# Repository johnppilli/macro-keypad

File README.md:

# Macro Keypad — Custom USB Mechanical Keypad (KiCad)

A custom 9-key (3×3) USB-C mechanical macro keypad, designed from schematic to
fabrication in KiCad around an **RP2040** microcontroller. This is my own design —
schematic capture, component selection, PCB layout, and fabrication.

## The fabricated board

| Top | Bottom |
| --- | --- |
|  |  |

*Bare 2-layer board from JLCPCB, prior to switch/component assembly.*

## Design highlights

- **RP2040** microcontroller with USB-C for both power and data
- **USBLC6** ESD protection on the USB data lines
- **3×3 matrix of 9 mechanical key switches**, each with a per-key diode for N-key
  rollover / anti-ghosting during matrix scanning
- Decoupling on each supply pin; crystal and supporting passives per the RP2040
  reference design
- **2-layer PCB**, board outline defined in Edge.Cuts, ERC/DRC clean
- Gerbers + drill files generated and **fabricated through JLCPCB**

## What's in this repo

- `macro-keypad.kicad_sch` / `.kicad_pcb` / `.kicad_pro` — the KiCad project
- `macro-keypad.pdf` — schematic PDF
- `gerbers/` — fabrication outputs
- `board-front.jpg` / `board-back.jpg` — photos of the fabricated board

## Status — in progress

Bare fabricated board is in hand. Currently:

- **Hand-soldering** the switches, per-key diodes, and supporting components onto the board
- **Writing the RP2040 firmware** — USB-HID keyboard with matrix scanning and debounce

Next up: bring-up and testing once assembly is complete.

## Tools

KiCad · JLCPCB

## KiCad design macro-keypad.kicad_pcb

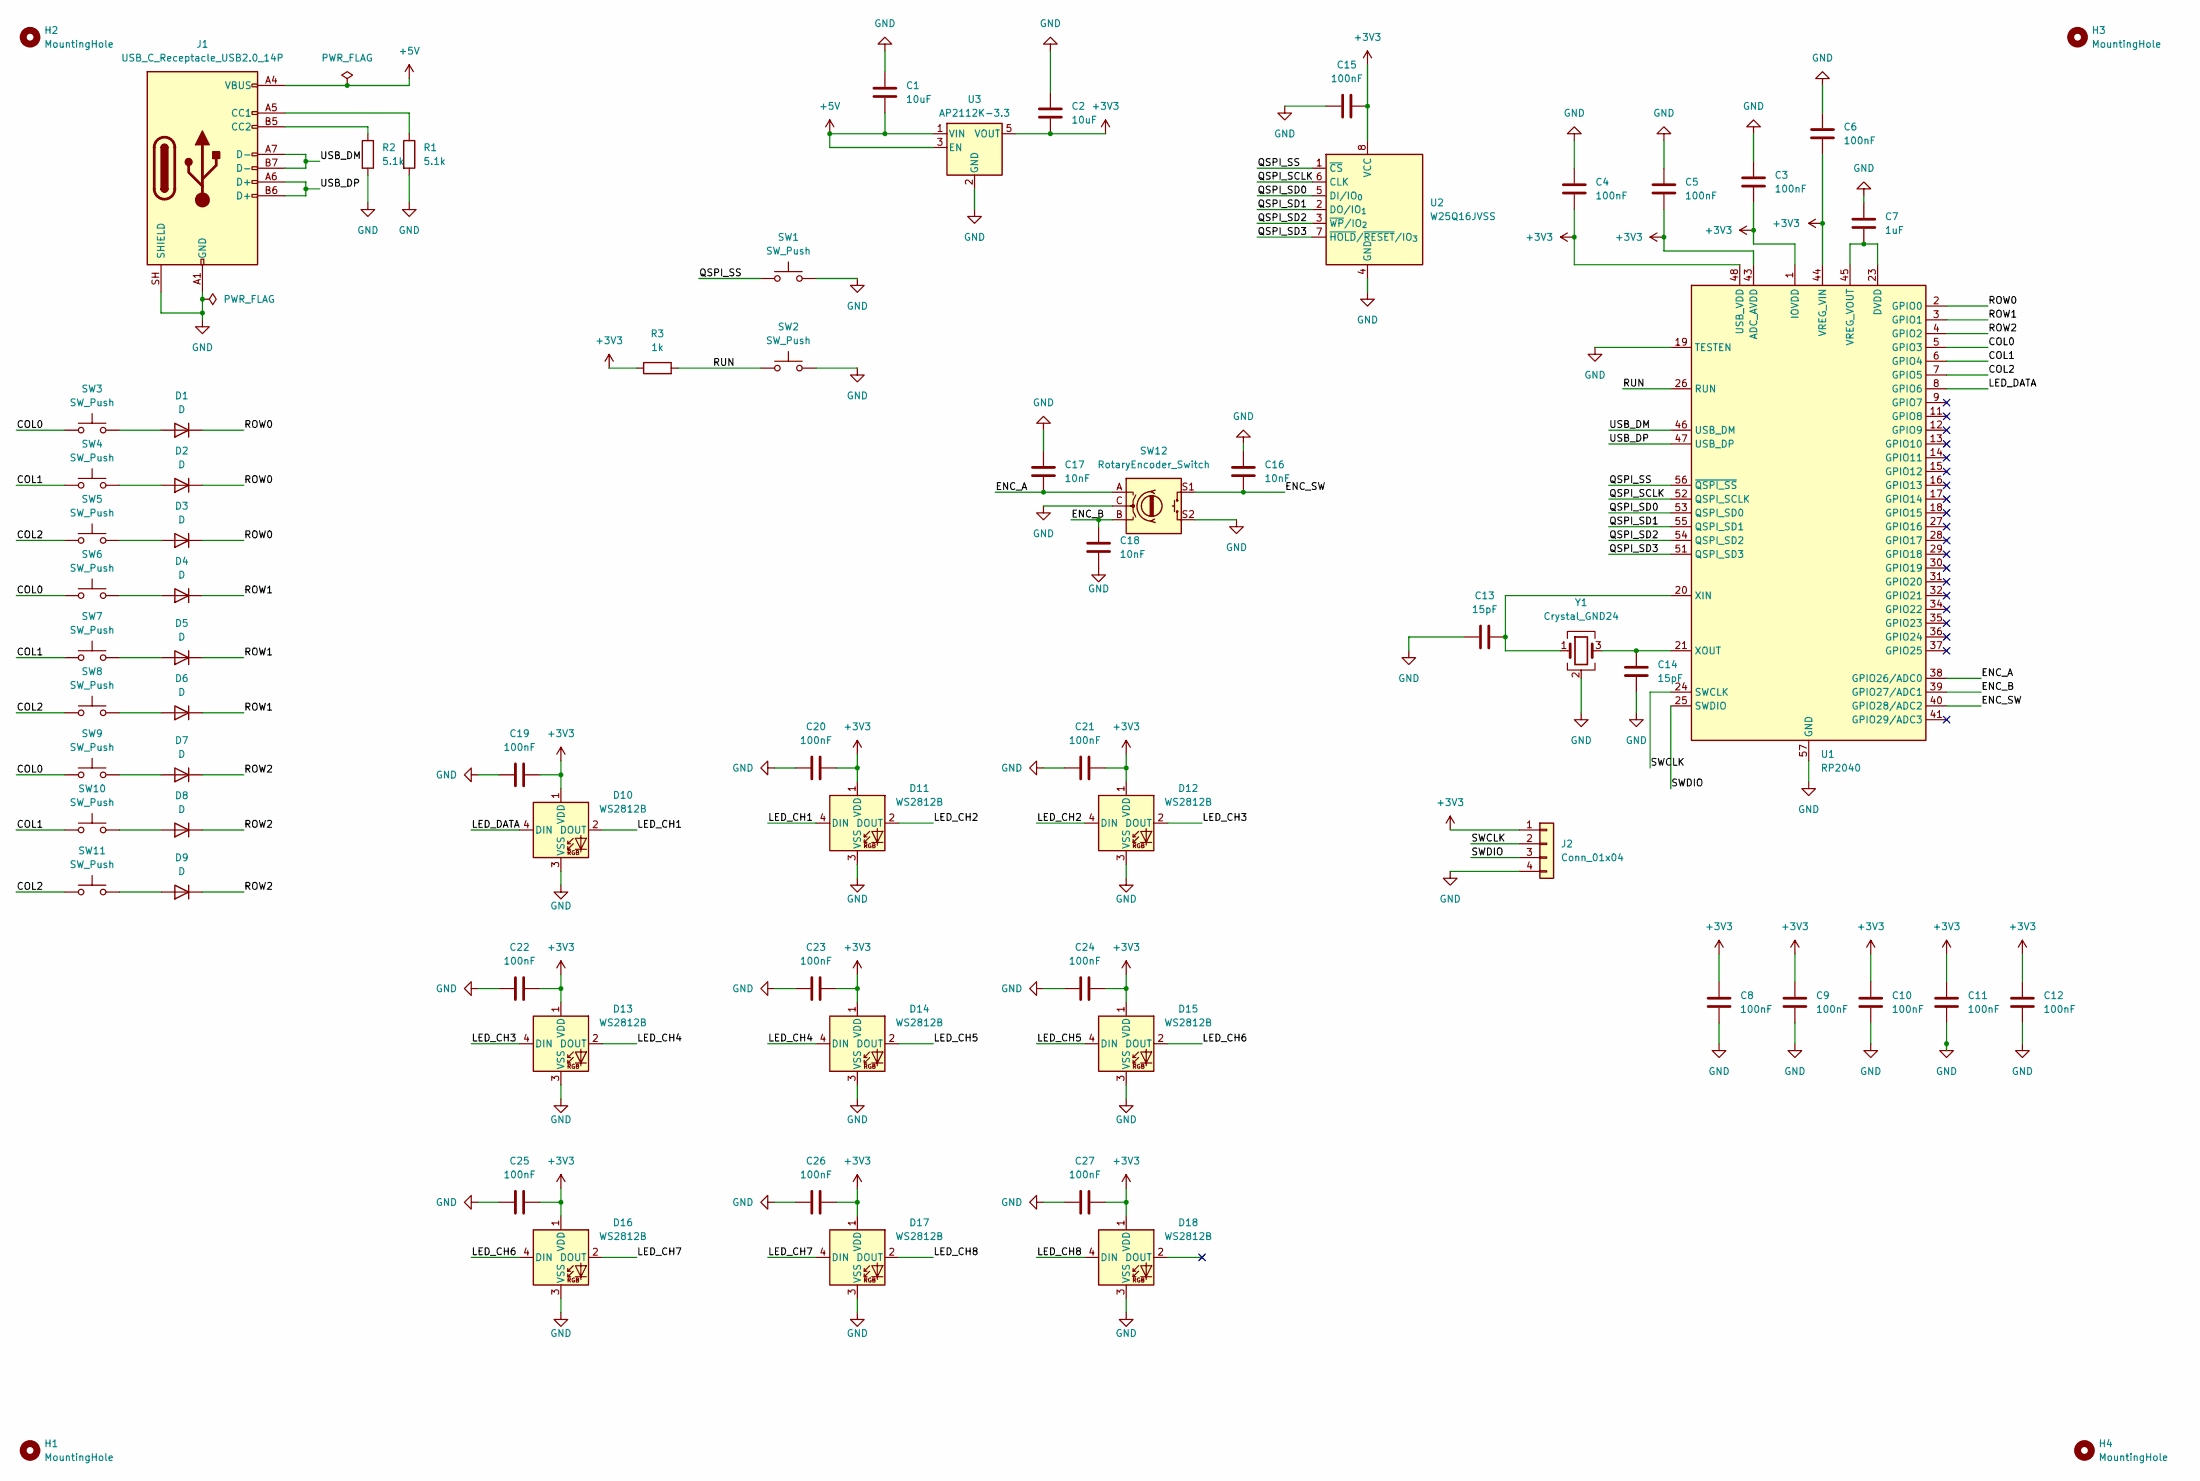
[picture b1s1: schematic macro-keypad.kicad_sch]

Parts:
C1, C2: 10uF; C_0603_1608Metric
C3, C4, C5, C6, C8, C9, C10, C11, C12, C15, C19, C20, C21, C22, C23, C24, C25, C26, C27: 100nF; C_0603_1608Metric
C7: 1uF; C_0603_1608Metric
C13, C14: 15pF; C_0603_1608Metric
C16, C17, C18: 10nF; C_0603_1608Metric
D1, D2, D3, D4, D5, D6, D7, D8, D9: D; D_SOD-123
D10, D11, D12, D13, D14, D15, D16, D17, D18: WS2812B; LED_WS2812B_PLCC4_5.0x5.0mm_P3.2mm
H1, H2, H3, H4: MountingHole; MountingHole_2.2mm_M2
J1: USB_C_Receptacle_USB2.0_14P; USB_C_Receptacle_GCT_USB4085
J2: Conn_01x04; PinHeader_1x04_P2.54mm_Vertical
R1, R2: 5.1k; R_0603_1608Metric
R3: 1k; R_0603_1608Metric
SW1, SW2: SW_Push; SW_PUSH_6mm
SW3, SW4, SW5, SW6, SW7, SW8, SW9, SW10, SW11: SW_Push; Kailh_socket_MX_optional
SW12: RotaryEncoder_Switch; RotaryEncoder_Alps_EC11E-Switch_Vertical_H20mm
U1: RP2040; QFN-56-1EP_7x7mm_P0.4mm_EP3.2x3.2mm
U2: W25Q16JVSS; SOIC-8_5.3x5.3mm_P1.27mm
U3: AP2112K-3.3; SOT-23-5
Y1: Crystal_GND24; Crystal_SMD_3225-4Pin_3.2x2.5mm

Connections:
+3V3: C2.1, C3.2, C4.2, C5.2, C6.2, C8.1, C9.1, C10.1, C11.1, C12.1, C15.2, C19.2, C20.2, C21.2, C22.2, C23.2, C24.2, C25.2, C26.2, C27.2, D10.1 (VDD), D11.1 (VDD), D12.1 (VDD), D13.1 (VDD), D14.1 (VDD), D15.1 (VDD), D16.1 (VDD), D17.1 (VDD), D18.1 (VDD), J2.1, R3.1, U1.1 (IOVDD), U1.10 (IOVDD), U1.22 (IOVDD), U1.33 (IOVDD), U1.42 (IOVDD), U1.43 (ADC_AVDD), U1.44 (VREG_VIN), U1.48 (USB_VDD), U1.49 (IOVDD), U2.8 (VCC), U3.5 (VOUT)
+5V: C1.2, J1.A4 (VBUS), J1.A9 (VBUS), J1.B4 (VBUS), J1.B9 (VBUS), U3.1 (VIN), U3.3 (EN)
/COL0: SW3.1, SW6.1, SW9.1, U1.5 (GPIO3)
/COL1: SW4.1, SW7.1, SW10.1, U1.6 (GPIO4)
/COL2: SW5.1, SW8.1, SW11.1, U1.7 (GPIO5)
/ENC_A: C17.2, SW12.A, U1.38 (GPIO26/ADC0)
/ENC_B: C18.1, SW12.B, U1.39 (GPIO27/ADC1)
/ENC_SW: C16.2, SW12.S1, U1.40 (GPIO28/ADC2)
/LED_CH1: D10.2 (DOUT), D11.4 (DIN)
/LED_CH2: D11.2 (DOUT), D12.4 (DIN)
/LED_CH3: D12.2 (DOUT), D13.4 (DIN)
/LED_CH4: D13.2 (DOUT), D14.4 (DIN)
/LED_CH5: D14.2 (DOUT), D15.4 (DIN)
/LED_CH6: D15.2 (DOUT), D16.4 (DIN)
/LED_CH7: D16.2 (DOUT), D17.4 (DIN)
/LED_CH8: D17.2 (DOUT), D18.4 (DIN)
/LED_DATA: D10.4 (DIN), U1.8 (GPIO6)
/QSPI_SCLK: U1.52 (QSPI_SCLK), U2.6 (CLK)
/QSPI_SD0: U1.53 (QSPI_SD0), U2.5 (DI/IO_{0})
/QSPI_SD1: U1.55 (QSPI_SD1), U2.2 (DO/IO_{1})
/QSPI_SD2: U1.54 (QSPI_SD2), U2.3 (~WP/IO_{2})
/QSPI_SD3: U1.51 (QSPI_SD3), U2.7 (~HOLD/~RESET/IO_{3})
/QSPI_SS: SW1.1, U1.56 (~QSPI_SS), U2.1 (~CS)
/ROW0: D1.1 (K), D2.1 (K), D3.1 (K), U1.2 (GPIO0)
/ROW1: D4.1 (K), D5.1 (K), D6.1 (K), U1.3 (GPIO1)
/ROW2: D7.1 (K), D8.1 (K), D9.1 (K), U1.4 (GPIO2)
/RUN: R3.2, SW2.1, U1.26 (RUN)
/SWCLK: J2.2, U1.24 (SWCLK)
/SWDIO: J2.3, U1.25 (SWDIO)
/USB_DM: J1.A7 (D-), J1.B7 (D-), U1.46 (USB_DM)
/USB_DP: J1.A6 (D+), J1.B6 (D+), U1.47 (USB_DP)
GND: C1.1, C2.2, C3.1, C4.1, C5.1, C6.1, C7.1, C8.2, C9.2, C10.2, C11.2, C12.2, C13.2, C14.2, C15.1, C16.1, C17.1, C18.2, C19.1, C20.1, C21.1, C22.1, C23.1, C24.1, C25.1, C26.1, C27.1, D10.3 (VSS), D11.3 (VSS), D12.3 (VSS), D13.3 (VSS), D14.3 (VSS), D15.3 (VSS), D16.3 (VSS), D17.3 (VSS), D18.3 (VSS), J1.A1 (GND), J1.A12 (GND), J1.B1 (GND), J1.B12 (GND), J1.SH (SHIELD), J2.4, R1.2, R2.2, SW1.2, SW2.2, SW12.C, SW12.S2, U1.19 (TESTEN), U1.57 (GND), U2.4 (GND), U3.2 (GND), Y1.2 (G), Y1.4 (G)
unnamed: D1.2 (A), SW3.2
unnamed: D2.2 (A), SW4.2
unnamed: D3.2 (A), SW5.2
unnamed: D4.2 (A), SW6.2
unnamed: D5.2 (A), SW7.2
unnamed: D6.2 (A), SW8.2
unnamed: D7.2 (A), SW9.2
unnamed: D8.2 (A), SW10.2
unnamed: D9.2 (A), SW11.2
unnamed: J1.A5 (CC1), R1.1
unnamed: J1.B5 (CC2), R2.1
unnamed: C7.2, U1.23 (DVDD), U1.45 (VREG_VOUT), U1.50 (DVDD)
unnamed: C13.1, U1.20 (XIN), Y1.1
unnamed: C14.1, U1.21 (XOUT), Y1.3

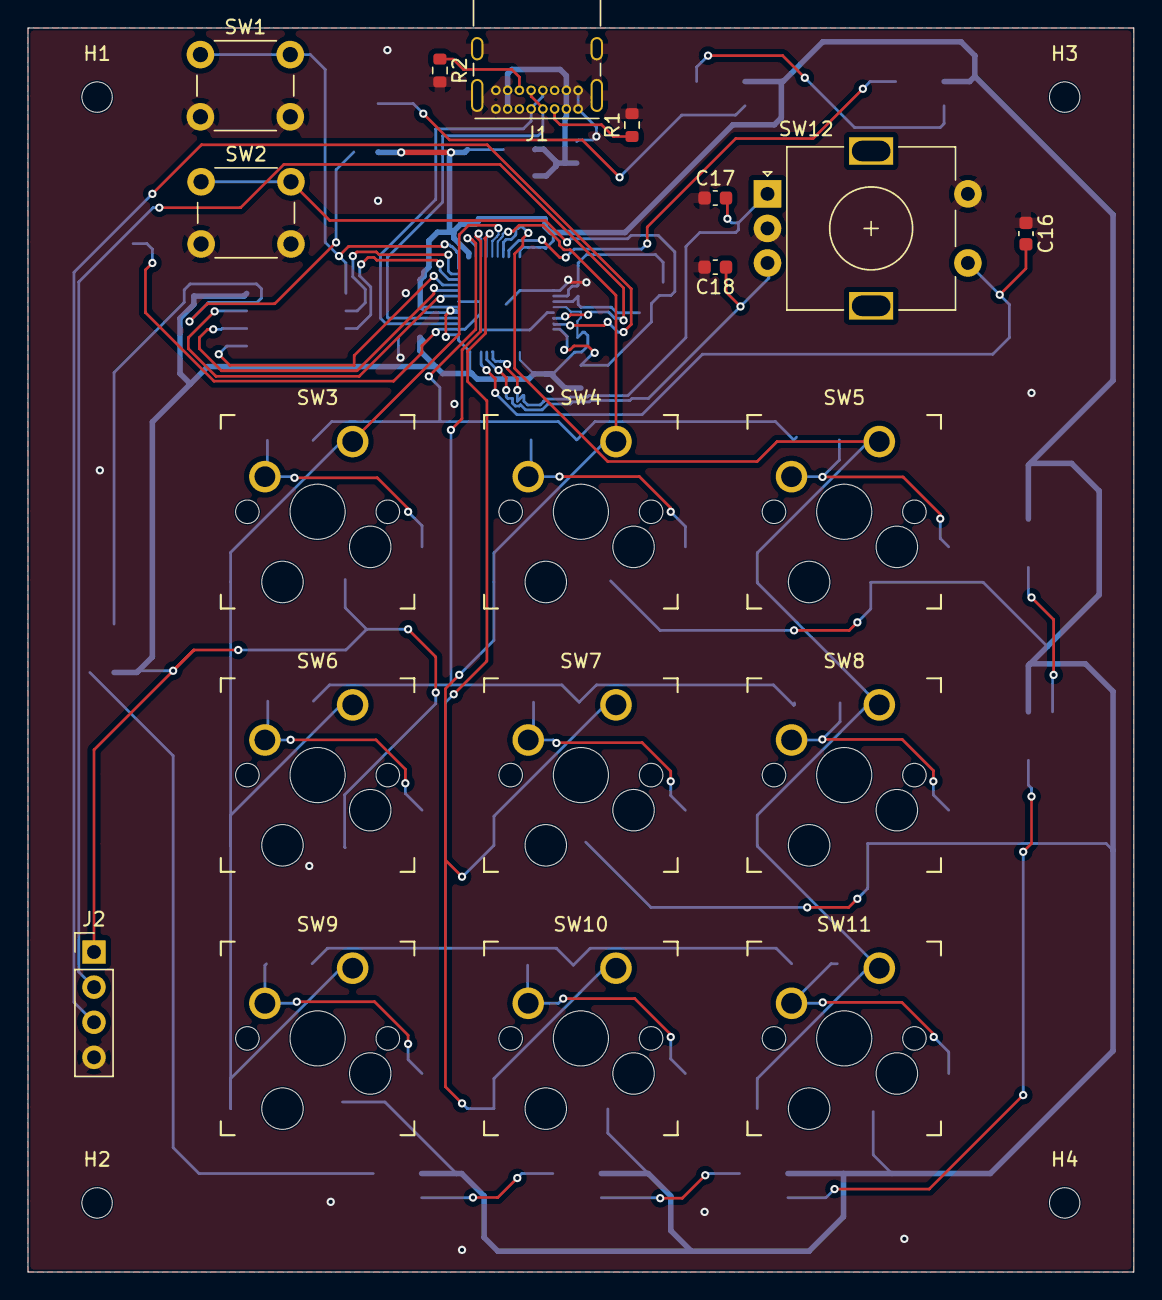
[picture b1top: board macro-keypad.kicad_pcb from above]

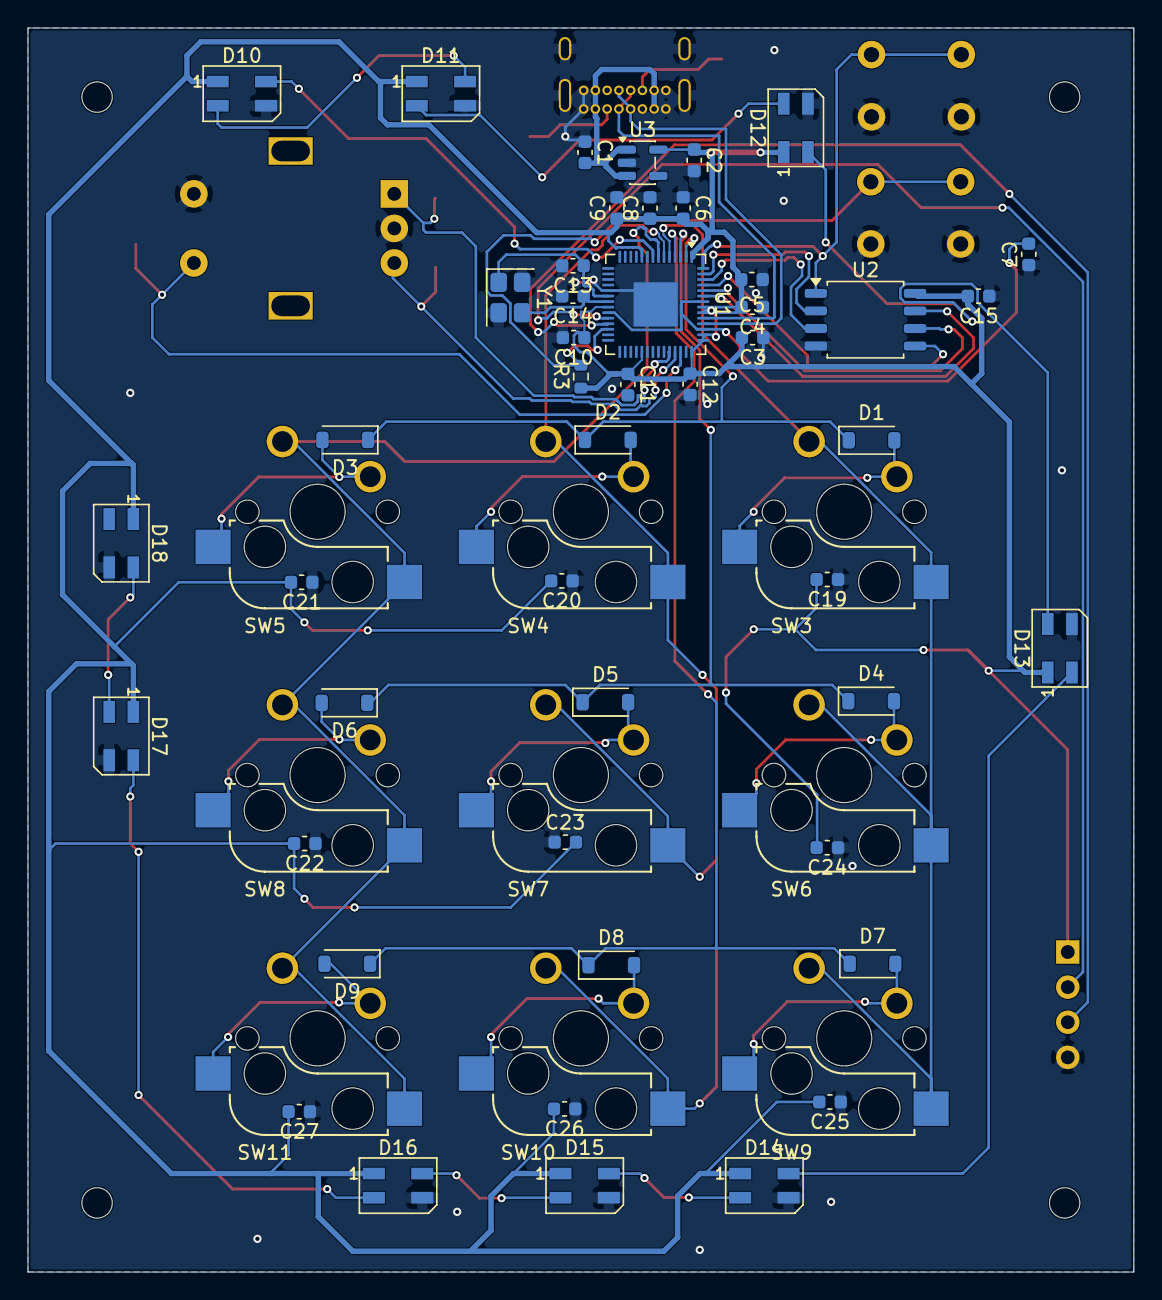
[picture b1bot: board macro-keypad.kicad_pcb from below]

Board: 2 copper layers, 80.0 x 90.0 mm, 70 parts (47 on the bottom side), 46 nets.

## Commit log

2026-06-26 Custom USB macro keypad - KiCad design + fabriated board
2026-06-26 Stop tracking editor local-history folder
2026-06-26 Add current status - assembly and firmware in progress
